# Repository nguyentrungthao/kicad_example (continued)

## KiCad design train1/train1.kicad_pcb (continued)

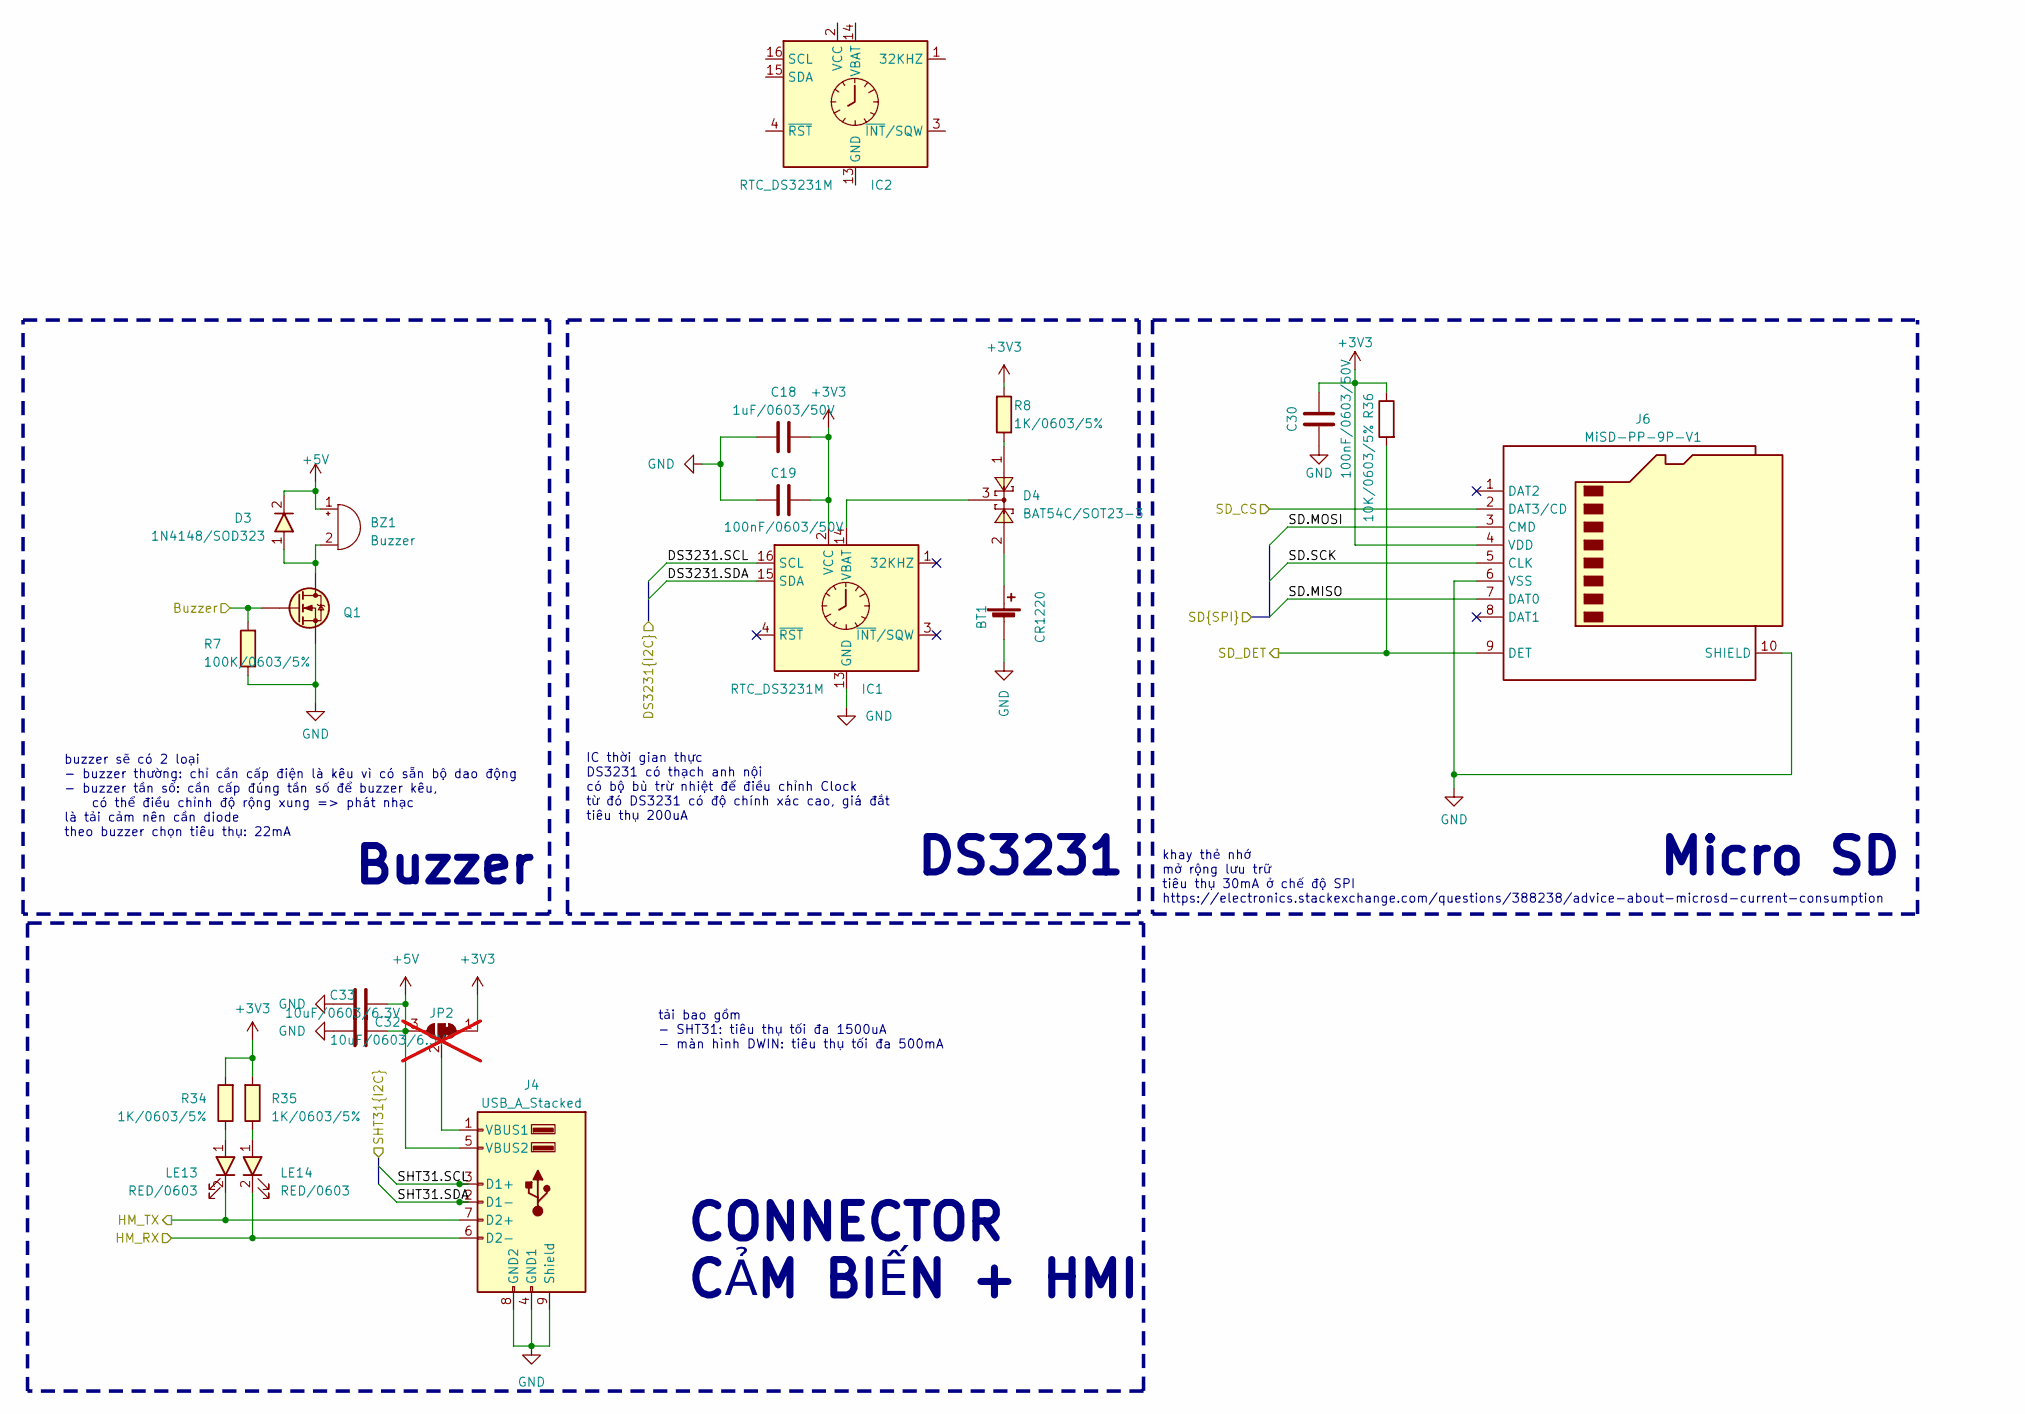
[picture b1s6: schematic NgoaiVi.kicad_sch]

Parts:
BT1: CR1220; BatteryHolder_CR1220
BZ1: Buzzer; Buzzer_12x9.5RM7.6
C18: 1uF/0603/50V; C_0603
C19, C30: 100nF/0603/50V; C_0603
C32, C33: 10uF/0603/6.3V; C_0603
D3: 1N4148/SOD323; D_SOD323
D4: BAT54C/SOT23-3; SOT23-3
IC1, IC2: RTC_DS3231M; SOIC-16W_7.5x10.3mm_P1.27mm
J4: USB_A_Stacked; USB_A_Wuerth_61400826021_Horizontal_Stacked
J6: MiSD-PP-9P-V1; MicroSD_Socket_9P
JP2: power select; SolderJumper-3_P1.3mm_Bridged12_RoundedPad1.0x1.5mm_NumberL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; not fitted
LE13, LE14: RED/0603; LED_0603
Q1: SI2300/SOT23-3; SOT23-3
R7: 100K/0603/5%; C_0603
R8, R34, R35: 1K/0603/5%; C_0603
R36: 10K/0603/5%; C_0603

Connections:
+3.3V: C18.2, C19.2, C30.2, IC1.2 (VCC), J6.4 (VDD), JP2.1 (A), R8.1, R34.1, R35.1, R36.1; also elsewhere on the board
+5V: BZ1.1 (-), C32.2, C33.2, D3.2, J4.5 (VBUS2), JP2.3 (B); also elsewhere on the board
/ESP32/ESP_CO2_RX: J4.7 (D2+), LE13.2; also elsewhere on the board
/ESP32/ESP_CO2_TX: J4.6 (D2-), LE14.2; also elsewhere on the board
/ESP32/ESP_SDCARD_CS: J6.2 (DAT3/CD); also elsewhere on the board
/ESP32/ESP_SDCARD_DET: J6.9 (DET), R36.2; also elsewhere on the board
/ESP32/ESP_SPI.MISO: J6.7 (DAT0); also elsewhere on the board
/ESP32/ESP_SPI.MOSI: J6.3 (CMD); also elsewhere on the board
/ESP32/ESP_SPI.SCK: J6.5 (CLK); also elsewhere on the board
Buzzer: Q1.1 (G), R7.1; also elsewhere on the board
GND: BT1.2 (-), C18.1, C19.1, C30.1, C32.1, C33.1, IC1.5 (GND), IC1.6 (GND), IC1.7 (GND), IC1.8 (GND), IC1.9 (GND), IC1.10 (GND), IC1.11 (GND), IC1.12 (GND), IC1.13 (GND), J4.4 (GND1), J4.8 (GND2), J4.9 (Shield), J6.6 (VSS), J6.10 (SHIELD), Q1.2 (S), R7.2; also elsewhere on the board
unnamed: BT1.1 (+), D4.2
unnamed: BZ1.2 (+), D3.1, Q1.3 (D)
unnamed: D4.1, R8.2
unnamed: D4.3, IC1.14 (VBAT)
unnamed: IC2.5 (GND), IC2.6 (GND), IC2.7 (GND), IC2.8 (GND), IC2.9 (GND), IC2.10 (GND), IC2.11 (GND), IC2.12 (GND), IC2.13 (GND)
unnamed: J4.1 (VBUS1), JP2.2 (C)
unnamed: LE13.1, R34.2
unnamed: LE14.1, R35.2

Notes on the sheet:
tải bao gồm - SHT31: tiêu thụ tối đa 1500uA - màn hình DWIN: tiêu thụ tối đa 500mA
Buzzer
CONNECTOR CẢM BIẾN + HMI
Micro SD
DS3231
buzzer sẽ có 2 loại - buzzer thường: chỉ cần cấp điện là kêu vì có sẵn bộ dao động - buzzer tần số: cần cấp đúng tần số để buzzer kêu, có thể điều chỉnh độ rộng xung => phát nhạc là tải cảm nên cần diode theo buzzer chọn tiêu thụ: 22mA
khay thẻ nhớ mở rộng lưu trữ tiêu thụ 30mA ở chế độ SPI https://electronics.stackexchange.com/questions/388238/advice-about-microsd-current-consumption
IC thời gian thực DS3231 có thạch anh nội có bộ bù trừ nhiệt để điều chỉnh Clock từ đó DS3231 có độ chính xác cao, giá đắt tiêu thụ 200uA

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
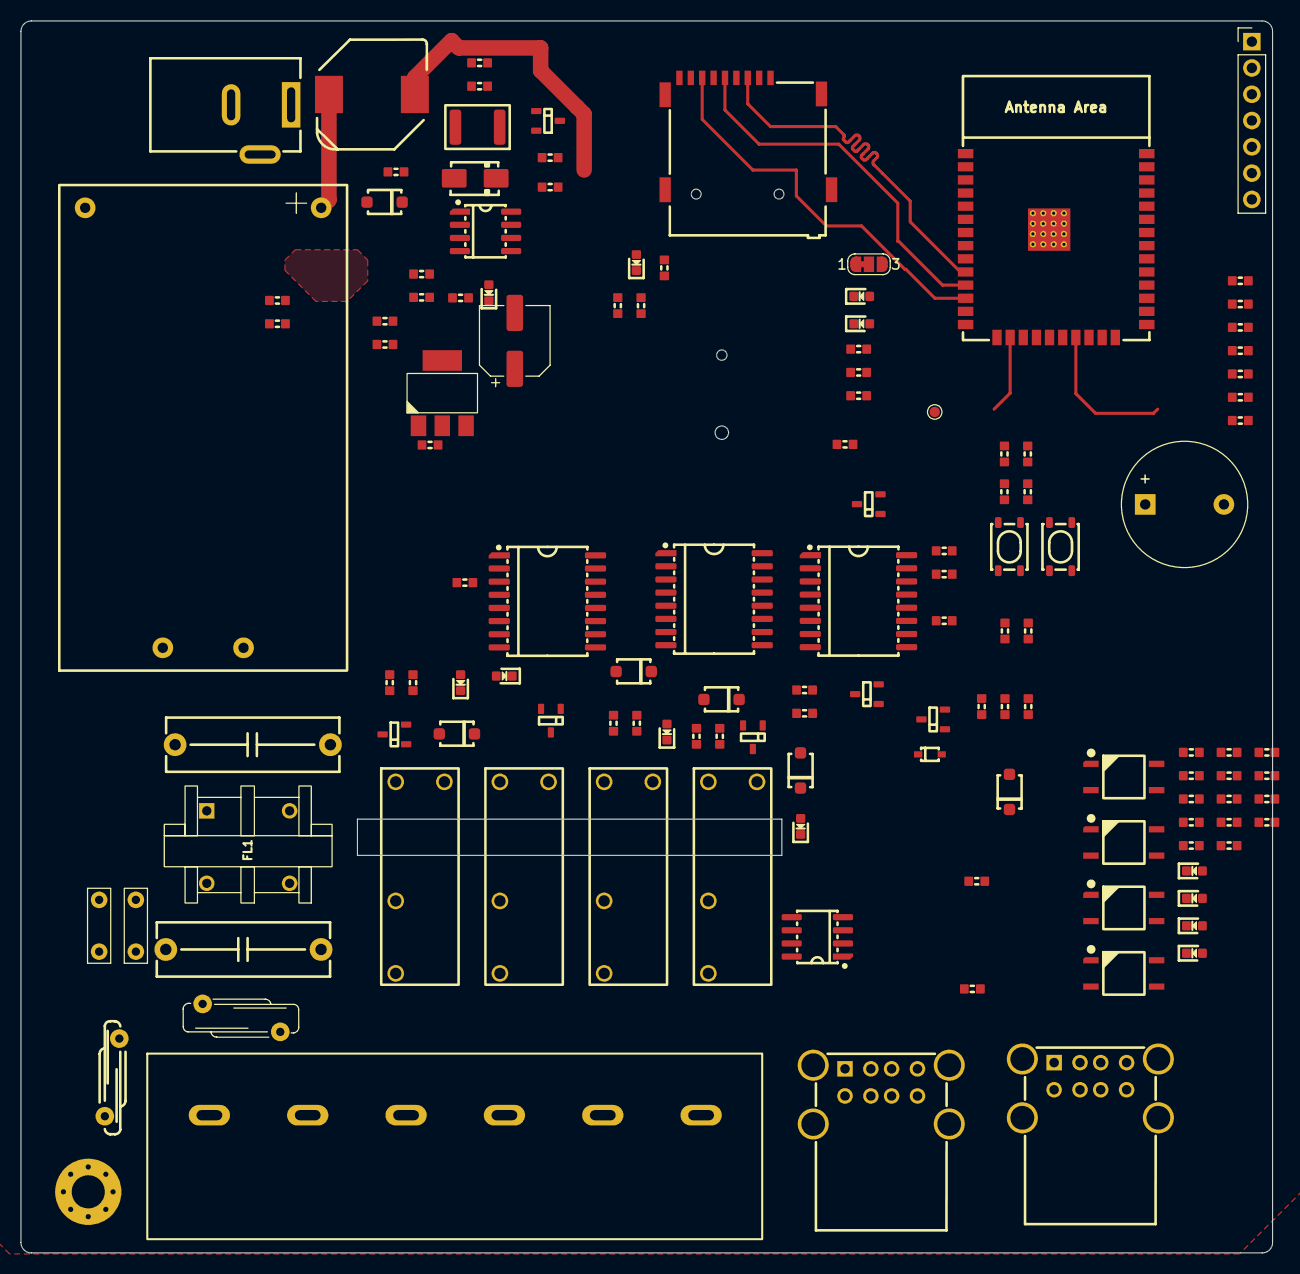
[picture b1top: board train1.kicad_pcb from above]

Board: 2 copper layers, 120.9 x 119.0 mm, 130 parts (1 on the bottom side), 79 nets.

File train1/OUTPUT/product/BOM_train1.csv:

"Reference","Value","Footprint","Qty","DNP","Thegioiic_Buylink"
"BT1","CR1220","trainFootprint:BatteryHolder_CR1220","1","","https://www.thegioiic.com/de-pin-cr1220-dan-smd"
"BZ1","Buzzer","trainFootprint:Buzzer_12x9.5RM7.6","1","","https://www.thegioiic.com/1209-buzzer-coi-chip-12x9mm-93db-xuyen-lo"
"C1,C3","0.1uF/275VAC","trainFootprint:C_Rect_L16.5mm_W5.0mm_P15.00mm_MKT","2","","https://www.thegioiic.com/tu-keo-vang-x2-100nf-0-1uf-104k-275vac"
"C2,C4","10nF/1000V","trainFootprint:C_Rect_L7.0mm_W2.0mm_P5.00mm","2","","https://www.thegioiic.com/tu-gom-xanh-10nf-1000v"
"C5","220uF/6.3x7.7/6.3V","trainFootprint:CP_Elec_6.3x7.7","1","","https://www.thegioiic.com/tu-nhom-smd-220uf-16v-6-3x7-7mm"
"C6,C9,C11,C25,C26,C29,C32,C33","10uF/0603/6.3V","trainFootprint:C_0603","8","","https://www.thegioiic.com/tu-gom-0603-10uf-16v"
"C7,C8,C15,C17,C19,C21,C22,C23,C24,C27,C28,C30","100nF/0603/50V","trainFootprint:C_0603","12","","https://www.thegioiic.com/tu-gom-0603-100nf-0-1uf-50v"
"C10,C12,C13,C14,C16,C18,C20","1uF/0603/50V","trainFootprint:C_0603","7","","https://www.thegioiic.com/tu-gom-0603-1uf-25v"
"C31","10nF/0603/50V","trainFootprint:C_0603","1","","https://www.thegioiic.com/tu-gom-0603-10nf-50v"
"D2","SS54/SMA","trainFootprint:D_SMA","1","","https://www.thegioiic.com/ss54-sma-diode-shotky-5a-40v"
"D3","1N4148/SOD323","trainFootprint:D_SOD323","1","","https://www.thegioiic.com/1n4148w-diode-chinh-luu-0-15a-75v-sod323"
"D4","BAT54C/SOT23-3","trainFootprint:SOT23-3","1","","https://www.thegioiic.com/bat54c"
"D5,D6,D7,D8","1N4007/SOD-123","trainFootprint:D_SOD-123","4","","https://www.thegioiic.com/1n4007w-a7-diode-chinh-luu-1a-1kv-sod-123"
"F1","300mA/250VAC","trainFootprint:RV_Disc_D12mm_W3.9mm_P7.5mm","1","","https://www.thegioiic.com/gr250-300-cau-chi-tu-phuc-hoi-250v-300ma"
"F2","0.9-1.2A/1812/24V","trainFootprint:Fuse_1812_4532Metric","1","","https://www.thegioiic.com/mf-msmf110-24x-2-cau-chi-tu-phuc-h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"
"FL1","10mH/UU9.8","trainFootprint:ACFilterChokeUU9.8","1","","https://www.thegioiic.com/cuon-cam-10mh-uu9-8-103"
"H1","MountingHole_Pad","trainFootprint:MountingHole_3.2mm_M3_Pad_Via","1","DNP",""
"IC1","RTC_DS3231M","trainFootprint:SOIC-16W_7.5x10.3mm_P1.27mm","1","","https://www.thegioiic.com/ds3231sn-ic-rtc-clock-calendar-16-soic"
"J1","DC5521/2.1mm","trainFootprint:BarrelJack_Wuerth_6941xx301002","1","","https://www.thegioiic.com/dc5521-dau-noi-nguon-dc-cai-5521-h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"
"J2,J4","USB_A_Stacked","trainFootprint:USB_A_Wuerth_61400826021_Horizontal_Stacked","2","","https://www.thegioiic.com/cong-usb-cai-doi-2-0-type-a-8-chan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"
"J3","HB9500-6P","trainFootprint:TerminalBlock_Screw_HB9500_6P_P9.5mm","1","","https://www.thegioiic.com/hb9500-6-terminal-khoi-han-pcb-6-c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"
"J5","header-2.54mm-7p","trainFootprint:PinHeader_1x07_P2.54mm_Vertical","1","","https://www.thegioiic.com/hang-rao-duc-don-2-54mm-40-chan-1-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"
"J6","MiSD-PP-9P-V1","trainFootprint:MicroSD_Socket_9P","1","","https://www.thegioiic.com/misd-pp-9p-v1-khay-the-nho-microsd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"
"JP2","power select","trainFootprint:SolderJumper-3_P1.3mm_Bridged12_RoundedPad1.0x1.5mm_NumberLabels","1","DNP",""
"L1","68uH 2A/10.4x10.4","trainFootprint:L_10.4x10.4_H4.8","1","","https://www.thegioiic.com/cuon-cam-dan-smd-cdrh104-1038-680-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"
"LE1,LE2,LE3,LE4,LE5,LE6,LE7,LE8,LE9,LE12,LE13,LE14","RED/0603","trainFootprint:LED_0603","12","","https://www.thegioiic.com/led-do-0603-dan-smd-trong-suot"
"PS1","HLK-10M05","trainFootprint:ACDC_HLK10M05","1","","https://www.thegioiic.com/hlk-10m05-chuyen-doi-ac-dc-220-5v-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"
"Q1,Q2,Q3,Q4,Q5","SI2300/SOT23-3","trainFootprint:SOT23-3","5","","https://www.thegioiic.com/si2300ds-mosfet-kenh-n-30v-3-6a-sot-23"
"Q6","SI2301/SOT23-3","trainFootprint:SOT23-3","1","","https://www.thegioiic.com/si2301ds-mosfet-kenh-p-20v-2-3a-sot-23-3"
"R1,R4,R6,R8,R9,R11,R13,R15,R19,R26,R29,R34,R35","1K/0603/5%","trainFootprint:C_0603","13","","https://www.thegioiic.com/dien-tro-1-kohm-0603-1-"
"R2,R7","100K/0603/5%","trainFootprint:C_0603","2","","https://www.thegioiic.com/dien-tro-100-kohm-0603-1-"
"R3,R10,R12,R14,R16,R18,R23,R28,R30,R31,R36","10K/0603/5%","trainFootprint:C_0603","11","","https://www.thegioiic.com/dien-tro-10-kohm-0603-1-"
"R5,R17,R20,R27","200R/0603/5%","trainFootprint:C_0603","4","","https://www.thegioiic.com/dien-tro-220-ohm-0603-1-"
"R21","9.1K/0603/1%","trainFootprint:C_0603","1","","https://www.thegioiic.com/dien-tro-9-1-kohm-0805-5-"
"R22","4.7K/0603/1%","trainFootprint:C_0603","1","","https://www.thegioiic.com/dien-tro-4-7-kohm-0603-1-"
"R32,R33","4.7K/0603/5%","trainFootprint:C_0603","2","","https://www.thegioiic.com/dien-tro-4-7-kohm-0603-1-"
"RL1,RL2,RL3,RL4","G5NB-1A-E_DC5","trainFootprint:Relay_G5NB-1A-E DC5","4","","https://www.thegioiic.com/g5nb-1a-e-5vdc-ro-le-5vdc-5a-spst-no"
"RV1","10D561","trainFootprint:RV_Disc_D12mm_W5.8mm_P7.5mm","1","","https://www.thegioiic.com/tu-chong-set-varistor-10d561k-560v"
"SW1,SW2","tactileSW/4.2x3.3","trainFootprint:SW_SPST_PTS810","2","","https://www.thegioiic.com/nut-nhan-4-2x3-3mm-cao-2-5mm-4-cha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"
"TP1","TestPoint","trainFootprint:TestPoint_Pad_D1.0mm","1","DNP",""
"U1","XL1509-5.0E1","trainFootprint:SOIC-8_3.9x4.9mm_P1.27mm","1","","https://www.thegioiic.com/xl1509-5-0e1-ic-on-ap-5v-2a-8-soic"
"U2","AMS1117-3.3","trainFootprint:SOT-223-3_TabPin2","1","","https://www.thegioiic.com/ams1117-3-3v-ic-on-ap-3-3v-1a-sot-223"
"U3","PCF8574/SOIC-16W","trainFootprint:SOIC-16W_7.5x10.3mm_P1.27mm","1","","https://www.thegioiic.com/pcf8574at-ic-i-o-expander-100khz-16-soic"
"U4","ACS712ELCTR-20A-T/SOIC-8","trainFootprint:SOIC-8_3.9x4.9mm_P1.27mm","1","","https://www.thegioiic.com/acs712elctr-20a-t-cam-bien-dong-20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"
"U5,U6,U8,U9","EL357N-G/SOP-4","trainFootprint:OPTO_EL357N-G","4","","https://www.thegioiic.com/el357n-g-optoisolator-transistor-o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"
"U7","B0505S-1W","IVS_FOOTPRINTS:B0505S","1","","https://www.thegioiic.com/b0505s-1wr3-chuyen-doi-dc-dc-vao-5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"
"U10","ESP32-WROOM-32E","trainFootprint:ESP32-WROOM-32E","1","","https://www.thegioiic.com/esp32-wroom-32e-n4-module-wifi-blu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"
"Z1,Z2","3.3V/SOD-123","trainFootprint:D_SOD-123","2","","https://www.thegioiic.com/bzt52h-c3v3-diode-zener-3-3v-375mw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"

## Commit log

2025-03-10 init Schematic
2025-03-10 READme
2025-03-10 update picture READme
2025-03-10 update color README
2025-03-10 update add library
2025-05-26 không có update
2025-07-16 thêm unit text newDWIN - dùng để test thư viện và gửi nhận nhanh các chuỗi cần thử qa serial
2025-09-18 fix(repo): delete backup file
